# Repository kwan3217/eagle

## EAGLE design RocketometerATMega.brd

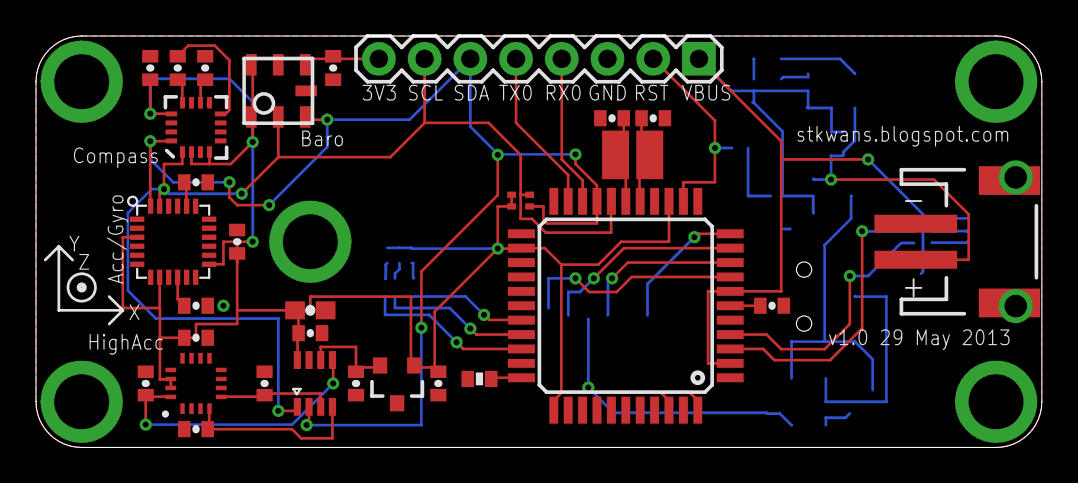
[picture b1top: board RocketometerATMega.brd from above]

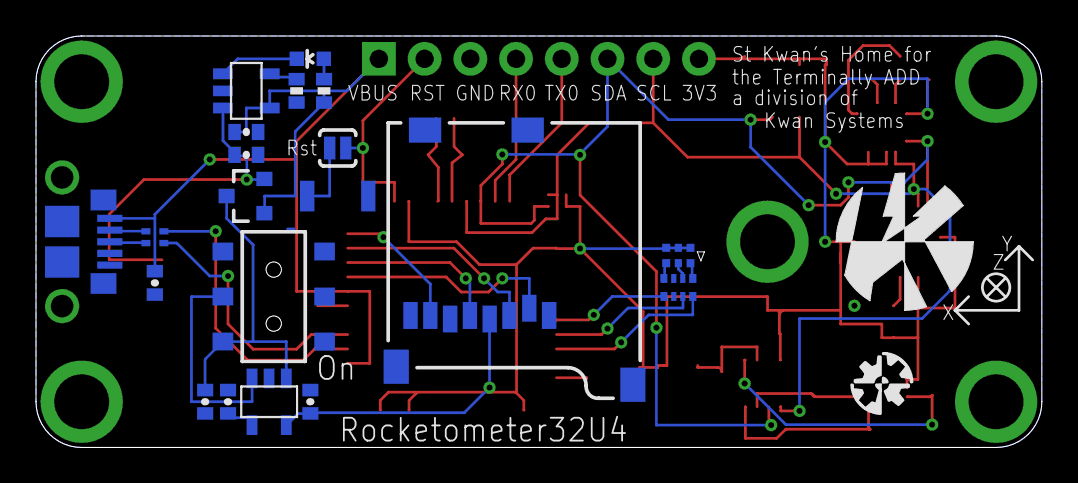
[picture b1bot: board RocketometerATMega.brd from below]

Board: 2 copper layers, 55.9 x 22.9 mm, 58 parts (22 on the bottom side), 43 nets.

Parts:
C101, C214, C610, C613, C802, C904, C905, C916, C917, C921: 100nF; 0402-CAP
C204, C406: 1uF; 0402-CAP
C215, C301, C302, C450, C810, C914, C922: 4.7uF; 0402-CAP
C416, C417: 22pF; 0402-CAP
C620: 2.2nF; 0402-CAP
C808: 220nF; 0402-CAP
C918: 10uF; 0603-CAP
D301: YELLOW; LED-0603
D302: DCC; SOT-23-3
D402: RGB; SMLP36
J301: JST 2mm; JST-2-SMD
J400: USB_MICROB_JSTGCT; USB_MICROB_3075
J401: M07; 1X08
J701: MICROSD-SOCKET; MICROSD-SOCKET-PP
JP1, JP2, JP3, JP4, JP5: STANDOFF
R301, R433: 10k; 0402-RES
R302: 1.5k; 0402-RES
R401: 10k; CRA02
R402: 1.5k; CRA04
R420: 22; CRA02
S201: AYZ0202
S457: B3U-1000P
S457A: SJ_2S-NO
U101: BMP180
U201: 3.3V; SOT-23-5
U301: MCP73831; SOT-23-5
U401: ATMEGA32U4TQFP; SPARKFUN-DIGITALIC_TQFP44
U601: MPU6050; MPU60X0
U801: HMC5883L; 16LPCC
U900: ADXL377
U910: AD7991; SOT-23-8
U920: MCP1525; SOT-23-3
U$4: AXES
U$5: KWAN_ACC
U$6: OSHW_ACC
Y401: 8MHz; CRYSTAL_SMD_3_2MM_2_5MM

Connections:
CS0: J701.2, U401.8
D+: J400.3, R420.2
D-: J400.2, R420.1
GND: C101.2, C204.2, C214.2, C215.2, C301.2, C302.2, C406.2, C416.1, C417.1, C450.2, C610.2, C613.1, C620.1, C802.2, C810.2, C904.2, C905.2, C914.2, C916.2, C917.2, C918.2, C921.2, C922.2, J301.1, J400.5, J400.P$1, J400.P$2, J400.P$3, J400.P$4, J400.P$8, J400.P$10, J401.3, J701.6, J701.CD2, J701.GND1, J701.GND3, JP1.P$1, JP2.P$1, JP3.P$1, JP4.P$1, JP5.P$1, R301.1, R433.1, S201.3, S457.P$2, U101.7, U201.2, U301.2, U401.5, U401.15, U401.23, U401.35, U401.43, U601.1, U601.9, U601.11, U601.18, U801.9, U801.11, U900.2, U900.6, U900.7, U910.7, U920.3
HWB: R433.2, U401.33
MISO0: J701.7, U401.11
MOSI0: J701.3, U401.10
unnamed: C620.2, U601.20
unnamed: R301.2, U301.5
unnamed: S457.P$1, S457A.1
unnamed: D301.C, U301.1
unnamed: D301.A, R302.1
unnamed: C922.1, U910.6, U920.2
unnamed: C610.1, U601.10
unnamed: C808.1, U801.8
unnamed: C808.2, U801.12
unnamed: C810.1, U801.10
unnamed: C214.1, U201.4
PWMB: R402.8, U401.31
PWMG: R402.7, U401.30
PWMR: R402.5, U401.29
PWR_EN: S201.2, U201.3
QWMB: D402.1, R402.1
QWMG: D402.3, R402.2
QWMR: D402.5, R402.4
RD+: R420.3, U401.4
RD-: R420.4, U401.3
RESET: J401.2, S457A.2, U401.13
RX0: J401.4, U401.20
SCK0: J701.5, U401.9
SCL0: J401.7, R401.2, U101.5, U401.18, U601.23, U801.1, U910.1
SDA0: J401.6, R401.1, U101.6, U401.19, U601.24, U801.16, U910.2
TX0: J401.5, U401.21
UCAP: C406.1, U401.6
VBUS: C302.1, C450.1, D302.1, J400.1, J401.1, R302.2, U301.4, U401.2, U401.7
VCC: C101.1, C215.1, C613.2, C802.1, C914.1, C917.1, C918.1, C921.1, D402.2, D402.4, D402.6, J401.8, J701.4, R401.3, R401.4, U101.2, U101.3, U201.5, U401.14, U401.24, U401.34, U401.42, U401.44, U601.3, U601.8, U601.13, U801.2, U801.4, U801.13, U900.14, U900.15, U910.8, U920.1
VIN: C204.1, D302.3, S201.1, U201.1
VLIPO: C301.1, D302.2, J301.2, U301.3
XACC: C905.1, U900.5, U910.3
XTAL1: C417.2, U401.17, Y401.2
XTAL2: C416.2, U401.16, Y401.1
YACC: C904.1, U900.4, U910.4
ZACC: C916.1, U900.16, U910.5

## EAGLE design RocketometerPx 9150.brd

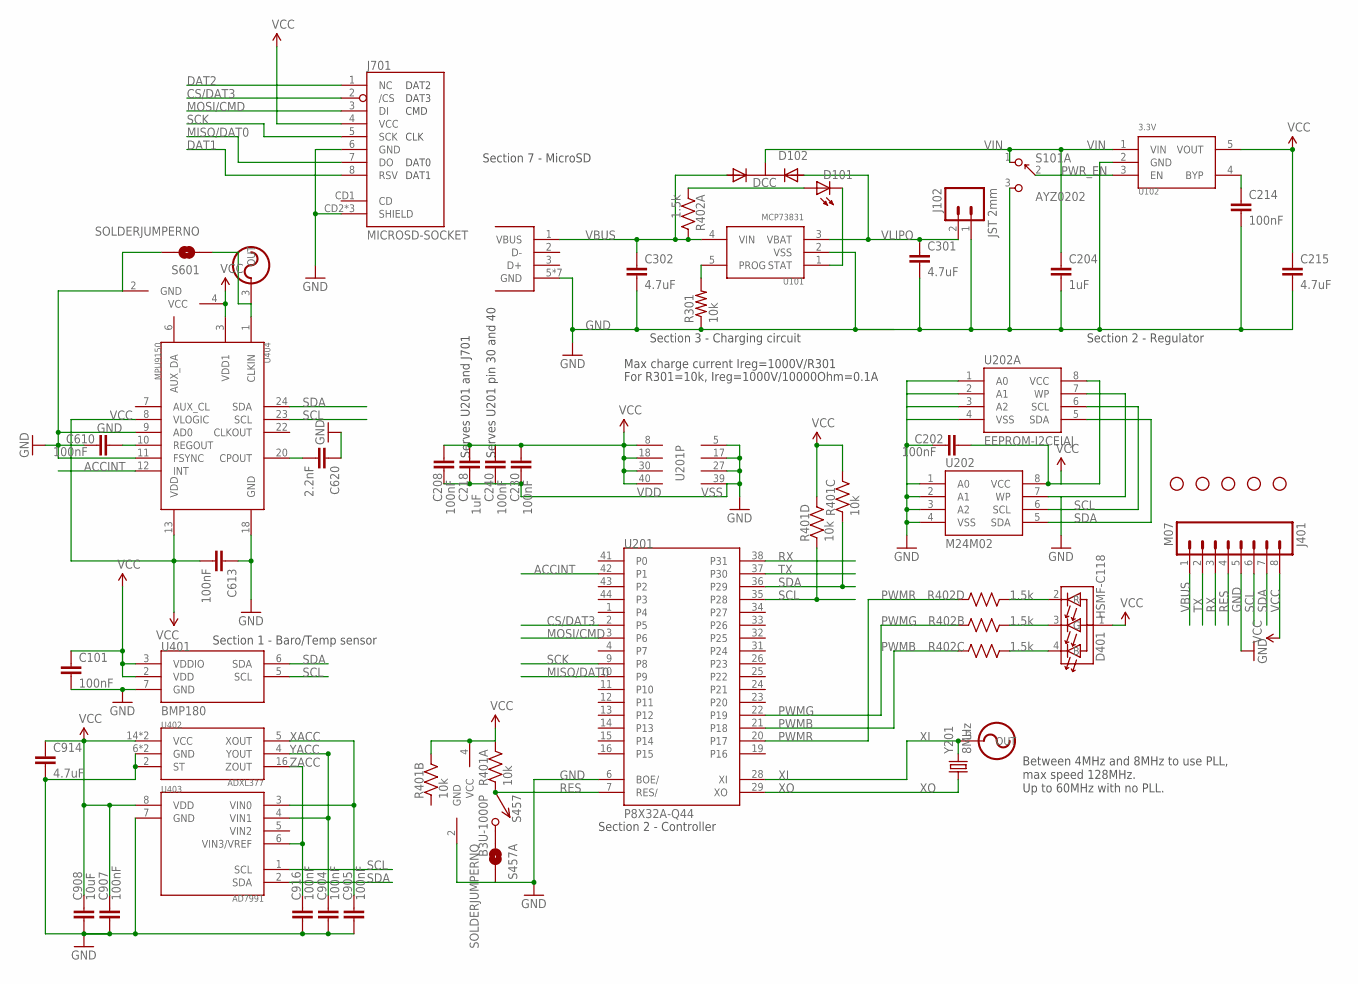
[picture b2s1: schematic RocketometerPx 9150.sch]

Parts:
C101, C202, C208, C214, C230, C240, C610, C613, C904, C905, C907, C916: 100nF; 0402-CAP; DIGIKEY 445-1265-1-ND
C204, C218: 1uF; 0402-CAP; DIGIKEY 445-4114-1-ND
C215, C301, C302, C914: 4.7uF; 0402-CAP; DIGIKEY 445-7395-1-ND
C620: 2.2nF; 0402-CAP; DIGIKEY 445-1257-1-ND
C908: 10uF; 0603-CAP; DIGIKEY 445-7486-1-ND
D101: YELLOW; LED-0603; DIGIKEY 350-2032-1-ND
D102: DCC; SOT-23-3; DIGIKEY 568-6500-1-ND
D401: HSMF-C118; DIGIKEY 516-1778-1-ND
J101: USB_MICROB_JSTGCT; USB_MICROB_3075; DIGIKEY 455-2562-1-ND
J102: JST 2mm; JST-2-SMD; DIGIKEY 455-1749-1-ND
J401: M07; 1X08; DIGIKEY $NOPART
J701: MICROSD-SOCKET; MICROSD-SOCKET-PP; DIGIKEY 101-00581-59-1-ND
JP1, JP2, JP3, JP4, JP5: STAND-OFFTIGHT; STAND-OFF-TIGHT; DIGIKEY $NOPART
R301: 10k; 0402-RES; DIGIKEY P10.0KLCT-ND
R401: 10k; CRA04; DIGIKEY CRA4S810KCT-ND
R402: 1.5k; CRA04; DIGIKEY CRA4S81.5KCT-ND
S101: AYZ0202; DIGIKEY 401-2013-1-ND
S457: B3U-1000P; DIGIKEY SW1020CT-ND
S457A, S601: SOLDERJUMPERNO; SJ_2S-NO; DIGIKEY $NOPART
U101: MCP73831; SOT-23-5; DIGIKEY 576-1910-1-ND
U102: 3.3V; SOT-23-5; DIGIKEY 576-1910-1-ND
U201: P8X32A-Q44; DIGIKEY P8X32A-Q44-ND
U202: M24M02; SO8N; DIGIKEY 497-11600-1-ND
U202A: EEPROM-I2CEIAJ; SO08-EIAJ; DIGIKEY $NOPART
U401: BMP180; DIGIKEY 828-1027-1-ND
U402: ADXL377; DIGIKEY ADXL377BCPZ-RL7CT-ND
U403: AD7991; SOT-23-8; DIGIKEY AD7991YRJZ-0500RL7CT-ND
U404: MPU9150; MPU60X0; DIGIKEY $NOPART
Y201: 8MHz; CRYSTAL_SMD_3_2MM_2_5MM; DIGIKEY 644-1178-1-ND
Y202: 8MHz; CRYSTAL_SMD_5MM_3_2MM
Y401: 19.2MHz; CRYSTAL_SMD_5MM_3_2MM

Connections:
ACCINT: U201.42 (P1), U404.12 (INT)
CS/DAT3: J701.2 (/CS), U201.2 (P5)
DAT1: J701.8 (RSV)
DAT2: J701.1 (NC)
GND: C101.2, C202.2, C204.2, C208.2, C214.2, C215.2, C218.2, C230.2, C240.2, C301.2, C302.2, C610.2, C613.1, C620.1, C904.2, C905.2, C907.2, C908.2, C914.2, C916.2, J101.5 (GND), J101.P$1 (GND), J101.P$2 (GND), J101.P$3 (GND), J101.P$4 (GND), J101.P$8 (GND), J101.P$10 (GND), J102.1, J401.5, J701.6 (GND), J701.CD2 (SHIELD), J701.GND1 (SHIELD), J701.GND3 (SHIELD), R301.1, S101.3, S457A.2, S601.2, U101.2 (VSS), U102.2 (GND), U201.5 (VSS), U201.6 (BOE/), U201.17 (VSS), U201.27 (VSS), U201.39 (VSS), U202.1 (A0), U202.2 (A1), U202.3 (A2), U202.4 (VSS), U202.7 (WP), U202A.1 (A0), U202A.2 (A1), U202A.3 (A2), U202A.4 (VSS), U202A.7 (WP), U401.7 (GND), U402.2 (ST), U402.6 (GND), U402.7 (GND), U403.7 (GND), U404.9 (AD0), U404.11 (FSYNC), U404.18 (GND), Y202.2 (GND), Y401.2 (GND)
MISO/DAT0: J701.7 (DO), U201.10 (P9)
MOSI/CMD: J701.3 (DI), U201.3 (P6)
unnamed: C620.2, U404.20 (CPOUT)
unnamed: R301.2, U101.5 (PROG)
unnamed: S601.1, U404.1 (CLKIN), Y401.3 (OUT)
unnamed: D101.C, U101.1 (STAT)
unnamed: D101.A, R402.1
unnamed: S457.P$2 (2), S457A.1
unnamed: C610.1, U404.10 (REGOUT)
unnamed: C214.1, U102.4 (BYP)
PWMB: R402.6 (2), U201.21 (P18)
PWMG: R402.7 (2), U201.22 (P19)
PWMR: R402.5 (2), U201.20 (P17)
PWR_EN: S101.2, U102.3 (EN)
QWMB: D401.4 (B), R402.3 (1)
QWMG: D401.3 (G), R402.2 (1)
QWMR: D401.2 (R), R402.4 (1)
RES: J401.4, R401.1, S457.P$1 (1), U201.7 (RES/)
RX: J401.3, U201.38 (P31)
SCK: J701.5 (SCK), U201.9 (P8)
SCL: J401.6, R401.4 (1), U201.35 (P28), U202.6 (SCL), U202A.6 (SCL), U401.5 (SCL), U403.1 (SCL), U404.23 (SCL)
SDA: J401.7, R401.3 (1), U201.36 (P29), U202.5 (SDA), U202A.5 (SDA), U401.6 (SDA), U403.2 (SDA), U404.24 (SDA)
TX: J401.2, U201.37 (P30)
VBUS: C302.1, D102.1 (A1), J101.1 (VBUS), J401.1, R402.8 (2), U101.4 (VIN)
VCC: C101.1, C202.1, C208.1, C215.1, C218.1, C230.1, C240.1, C613.2, C907.1, C908.1, C914.1, D401.1 (A), J401.8, J701.4 (VCC), R401.5 (2), R401.6 (2), R401.7 (2), R401.8 (2), U102.5 (VOUT), U201.8 (VDD), U201.18 (VDD), U201.30 (VDD), U201.40 (VDD), U202.8 (VCC), U202A.8 (VCC), U401.2 (VDD), U401.3 (VDDIO), U402.14 (VCC), U402.15 (VCC), U403.8 (VDD), U404.3 (VDD1), U404.8 (VLOGIC), U404.13 (VDD), Y202.4 (VCC), Y401.4 (VCC)
VIN: C204.1, D102.3 (K), S101.1, U102.1 (VIN)
VLIPO: C301.1, D102.2 (A2), J102.2, U101.3 (VBAT)
XACC: C905.1, U402.5 (XOUT), U403.3 (VIN0)
XI: U201.28 (XI), Y201.2, Y202.3 (OUT)
XO: U201.29 (XO), Y201.1
YACC: C904.1, U402.4 (YOUT), U403.4 (VIN1)
ZACC: C916.1, U402.16 (ZOUT), U403.6 (VIN3/VREF)

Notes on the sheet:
Section 2 - Regulator
Section 3 - Charging circuit
Section 7 - MicroSD
Section 1 - Baro/Temp sensor
Max charge current Ireg=1000V/R301
For R301=10k, Ireg=1000V/10000Ohm=0.1A
Section 2 - Controller
Serves U201 and J701
Serves U201 pin 30 and 40
Between 4MHz and 8MHz to use PLL, max speed 128MHz. Up to 60MHz with no PLL.

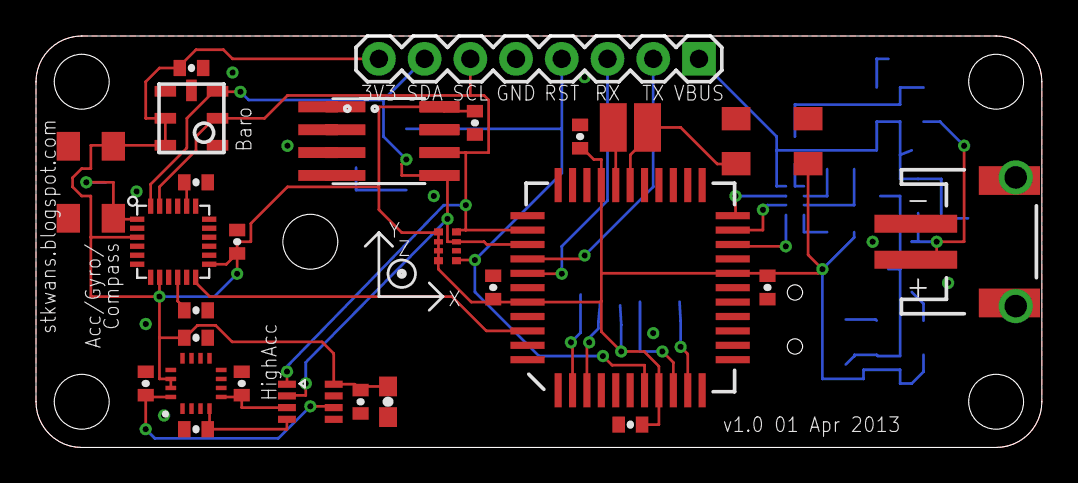
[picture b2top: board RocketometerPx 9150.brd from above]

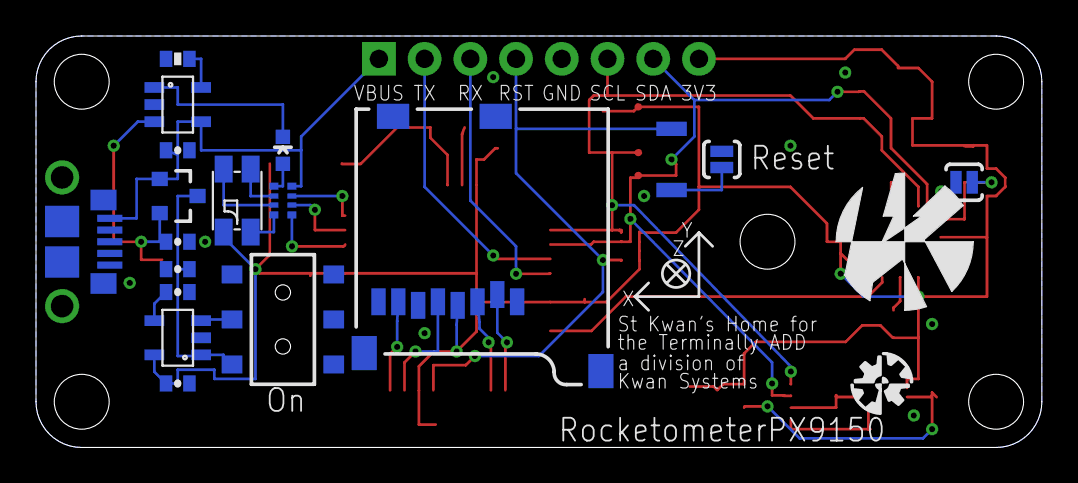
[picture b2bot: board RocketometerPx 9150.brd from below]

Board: 2 copper layers, 55.9 x 22.9 mm, 54 parts (20 on the bottom side), 35 nets.

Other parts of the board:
U$4: AXES
U$5: KWAN_ACC
U$6: OSHW_ACC

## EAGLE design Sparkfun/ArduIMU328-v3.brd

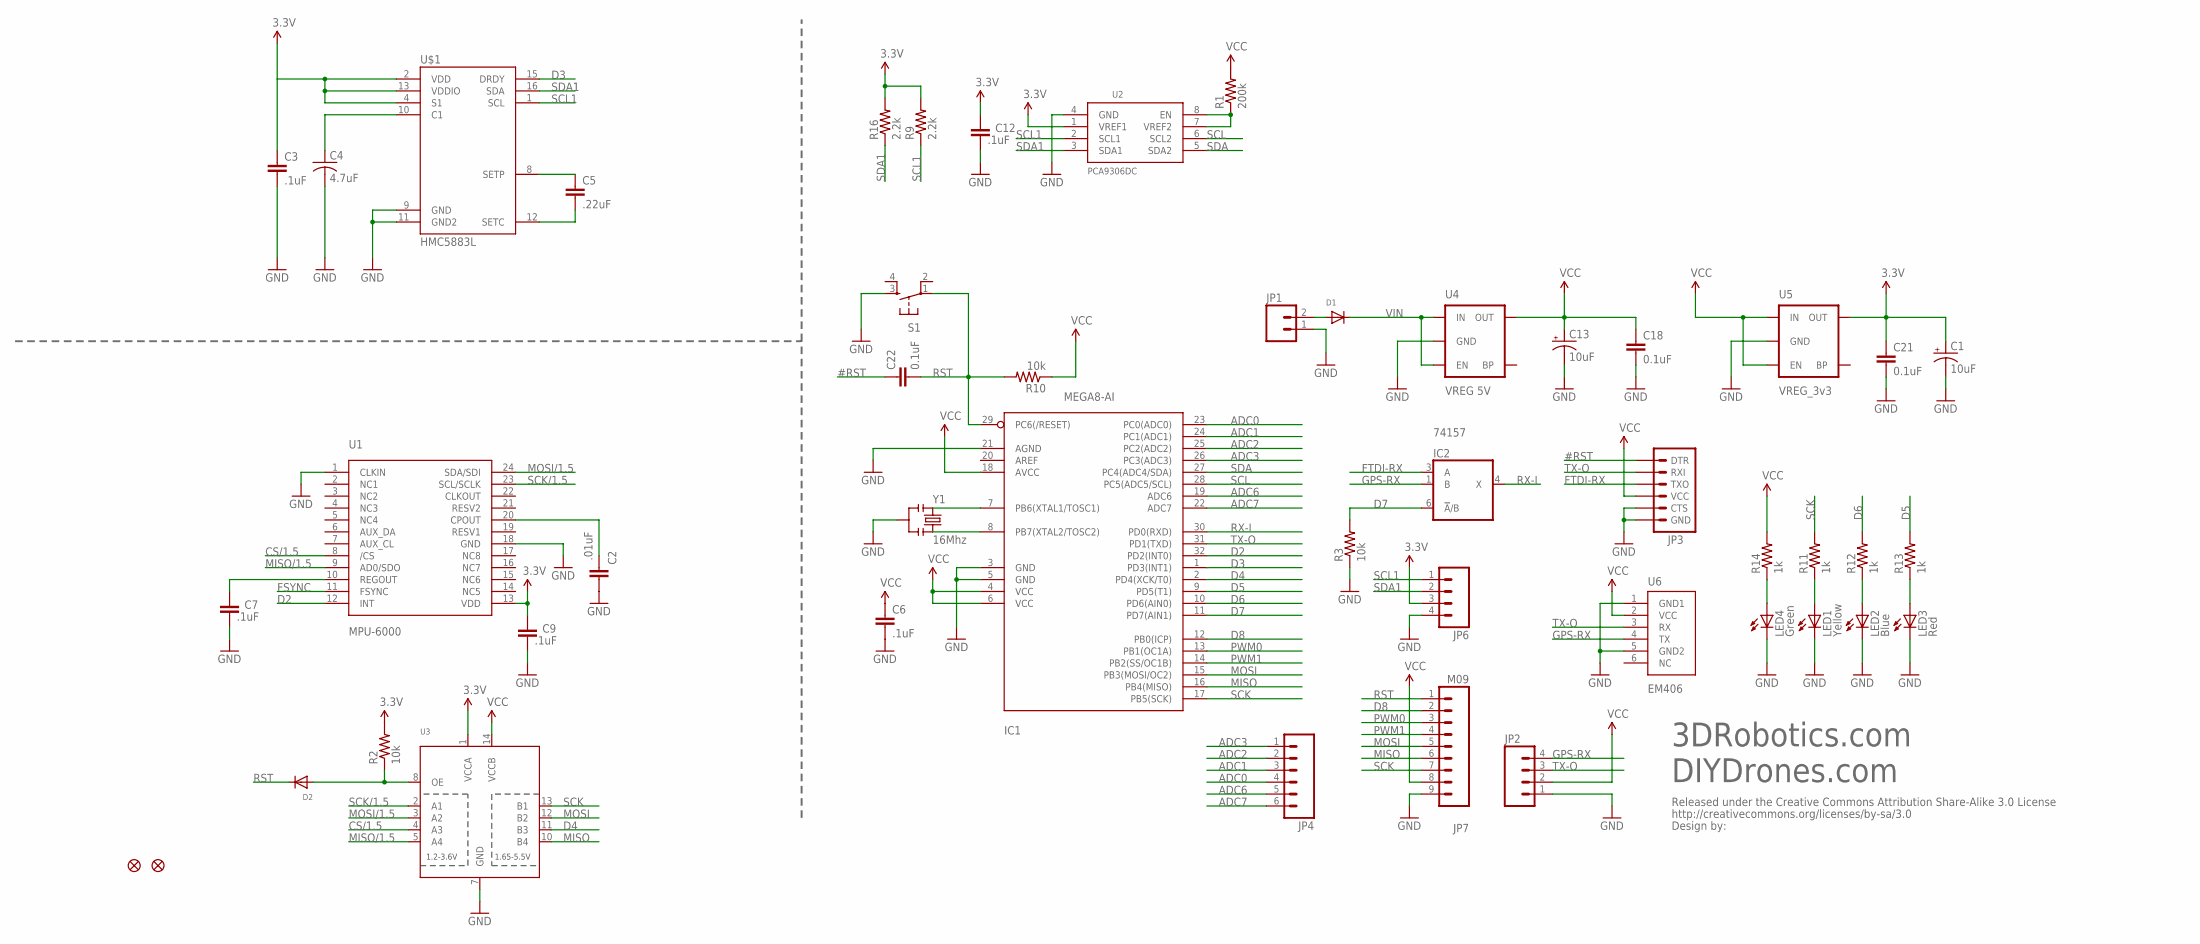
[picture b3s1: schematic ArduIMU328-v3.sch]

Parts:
C1, C13: 10uF; EIA3216
C2: .01uF; C0402
C3, C6: .1uF; 0402-CAP
C4: 4.7uF; C1206
C5: .22uF; 0402-CAP
C7, C9, C12: .1uF; C0402
C18, C21, C22: 0.1uF; 0402-CAP
D1, D2: DIODESOD-123; SOD-123
IC1: MEGA8-AI; TQFP32-08
IC2: 74157; DBV_R-PDSO-G6
JP1: M02PTH; 1X02
JP2, JP6: M04PTH; 1X04
JP3: ARDUINO_SERIAL_PROGRAMPTH; 1X06
JP4: M06SIP; 1X06
JP5, JP8: FIDUCIAL1X2; FIDUCIAL-1X2
JP7: M09; 1X09
LED1: Yellow; LED-0603
LED2: Blue; LED-0603
LED3: Red; LED-0603
LED4: Green; LED-0603
R1: 200k; C0402
R2, R3, R10: 10k; 0402-RES
R9, R16: 2.2k; C0402
R11, R12, R13, R14: 1k; 0402-RES
S1: TAC_SWITCHSMD; TACTILE_SWITCH_SMD
U1: MPU-6000; QFN-24
U2: PCA9306DC; VSSOP8
U3: TXB0104PWR; TSSOP14
U4: VREG 5V; SOT23-5
U5: VREG_3v3; SOT23-5
U6: EM406
U$1: HMC5883L; LPCC16
U$2: CREATIVE_COMMONS
Y1: 16Mhz; RESONATOR-SMD

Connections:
3.3V: C1.A (+), C3.1, C9.2, C12.2, C21.1, JP6.3, R2.2, R9.2, R16.2, U1.13 (VDD), U2.1 (VREF1), U3.1 (VCCA), U5.5 (OUT), U$1.2 (VDD), U$1.4 (S1), U$1.13 (VDDIO)
#RST: C22.1, JP3.1 (DTR)
ADC0: IC1.23 (PC0(ADC0)), JP4.4
ADC1: IC1.24 (PC1(ADC1)), JP4.3
ADC2: IC1.25 (PC2(ADC2)), JP4.2
ADC3: IC1.26 (PC3(ADC3)), JP4.1
ADC6: IC1.19 (ADC6), JP4.5
ADC7: IC1.22 (ADC7), JP4.6
CS/1.5: U1.8 (/CS), U3.4 (A3)
D2: IC1.32 (PD2(INT0)), U1.12 (INT)
D3: IC1.1 (PD3(INT1)), U$1.15 (DRDY)
D4: IC1.2 (PD4(XCK/T0)), U3.11 (B3)
D5: IC1.9 (PD5(T1)), R13.2
D6: IC1.10 (PD6(AIN0)), R12.2
D7: IC1.11 (PD7(AIN1)), IC2.6 (!A!/B), R3.2
D8: IC1.12 (PB0(ICP)), JP7.2
FSYNC: U1.11 (FSYNC)
FTDI-RX: IC2.3 (A), JP3.3 (TXO)
GND: C1.C (-), C2.1, C3.2, C4.2, C6.2, C7.1, C9.1, C12.1, C13.C (-), C18.2, C21.2, IC1.3 (GND), IC1.5 (GND), IC1.21 (AGND), IC2.2 (GND), JP1.1, JP2.1, JP3.5 (CTS), JP3.6 (GND), JP6.4, JP7.9, LED1.C, LED2.C, LED3.C, LED4.C, R3.1, S1.3, U1.1 (CLKIN), U1.18 (GND), U2.4 (GND), U3.7 (GND), U4.2 (GND), U5.2 (GND), U6.1 (GND1), U6.5 (GND2), U$1.9 (GND), U$1.11 (GND2), Y1.2
GPS-RX: IC2.1 (B), JP2.4, U6.4 (TX)
MISO: IC1.16 (PB4(MISO)), JP7.6, U3.10 (B4)
MISO/1.5: U1.9 (AD0/SDO), U3.5 (A4)
MOSI: IC1.15 (PB3(MOSI/OC2)), JP7.5, U3.12 (B2)
MOSI/1.5: U1.24 (SDA/SDI), U3.3 (A2)
unnamed: R1.1, U2.7 (VREF2), U2.8 (EN)
unnamed: C2.2, U1.20 (CPOUT)
unnamed: C7.2, U1.10 (REGOUT)
unnamed: C4.1, U$1.10 (C1)
unnamed: IC1.7 (PB6(XTAL1/TOSC1)), Y1.1
unnamed: C5.1, U$1.8 (SETP)
unnamed: IC1.8 (PB7(XTAL2/TOSC2)), Y1.3
unnamed: C5.2, U$1.12 (SETC)
unnamed: D2.A, R2.1, U3.8 (OE)
unnamed: LED1.A, R11.1
unnamed: LED2.A, R12.1
unnamed: LED3.A, R13.1
unnamed: D1.A, JP1.2
unnamed: LED4.A, R14.1
PWM0: IC1.13 (PB1(OC1A)), JP7.3
PWM1: IC1.14 (PB2(SS/OC1B)), JP7.4
RST: C22.2, D2.C, IC1.29 (PC6(/RESET)), JP7.1, R10.2, S1.1
RX-I: IC1.30 (PD0(RXD)), IC2.4 (X)
SCK: IC1.17 (PB5(SCK)), JP7.7, R11.2, U3.13 (B1)
SCK/1.5: U1.23 (SCL/SCLK), U3.2 (A1)
SCL: IC1.28 (PC5(ADC5/SCL)), U2.6 (SCL2)
SCL1: JP6.1, R9.1, U2.2 (SCL1), U$1.1 (SCL)
SDA: IC1.27 (PC4(ADC4/SDA)), U2.5 (SDA2)
SDA1: JP6.2, R16.1, U2.3 (SDA1), U$1.16 (SDA)
TX-O: IC1.31 (PD1(TXD)), JP2.3, JP3.2 (RXI), U6.3 (RX)
VCC: C6.1, C13.A (+), C18.1, IC1.4 (VCC), IC1.6 (VCC), IC1.18 (AVCC), IC2.5 (VCC), JP2.2, JP3.4 (VCC), JP7.8, R1.2, R10.1, R14.2, U3.14 (VCCB), U4.5 (OUT), U5.1 (IN), U5.3 (EN), U6.2 (VCC)
VIN: D1.C, U4.1 (IN), U4.3 (EN)

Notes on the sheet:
DIYDrones.com
3DRobotics.com

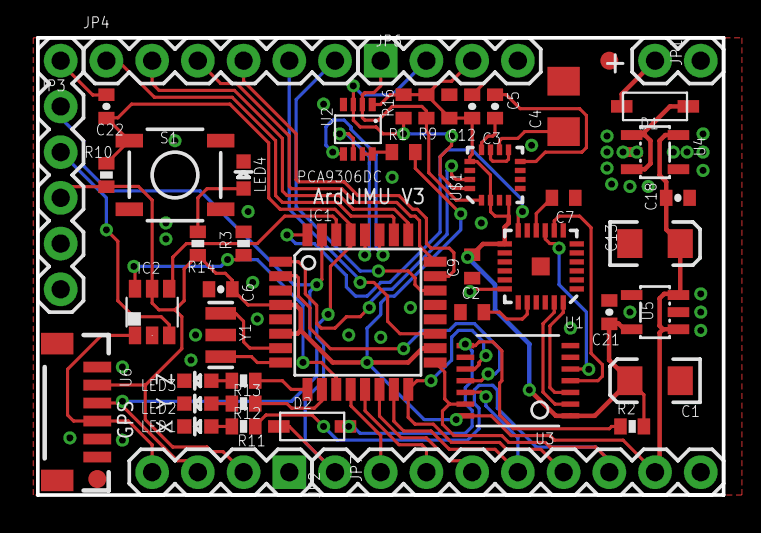
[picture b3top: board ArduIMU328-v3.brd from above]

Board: 4 copper layers, 38.1 x 25.4 mm, 49 parts (0 on the bottom side), 50 nets.

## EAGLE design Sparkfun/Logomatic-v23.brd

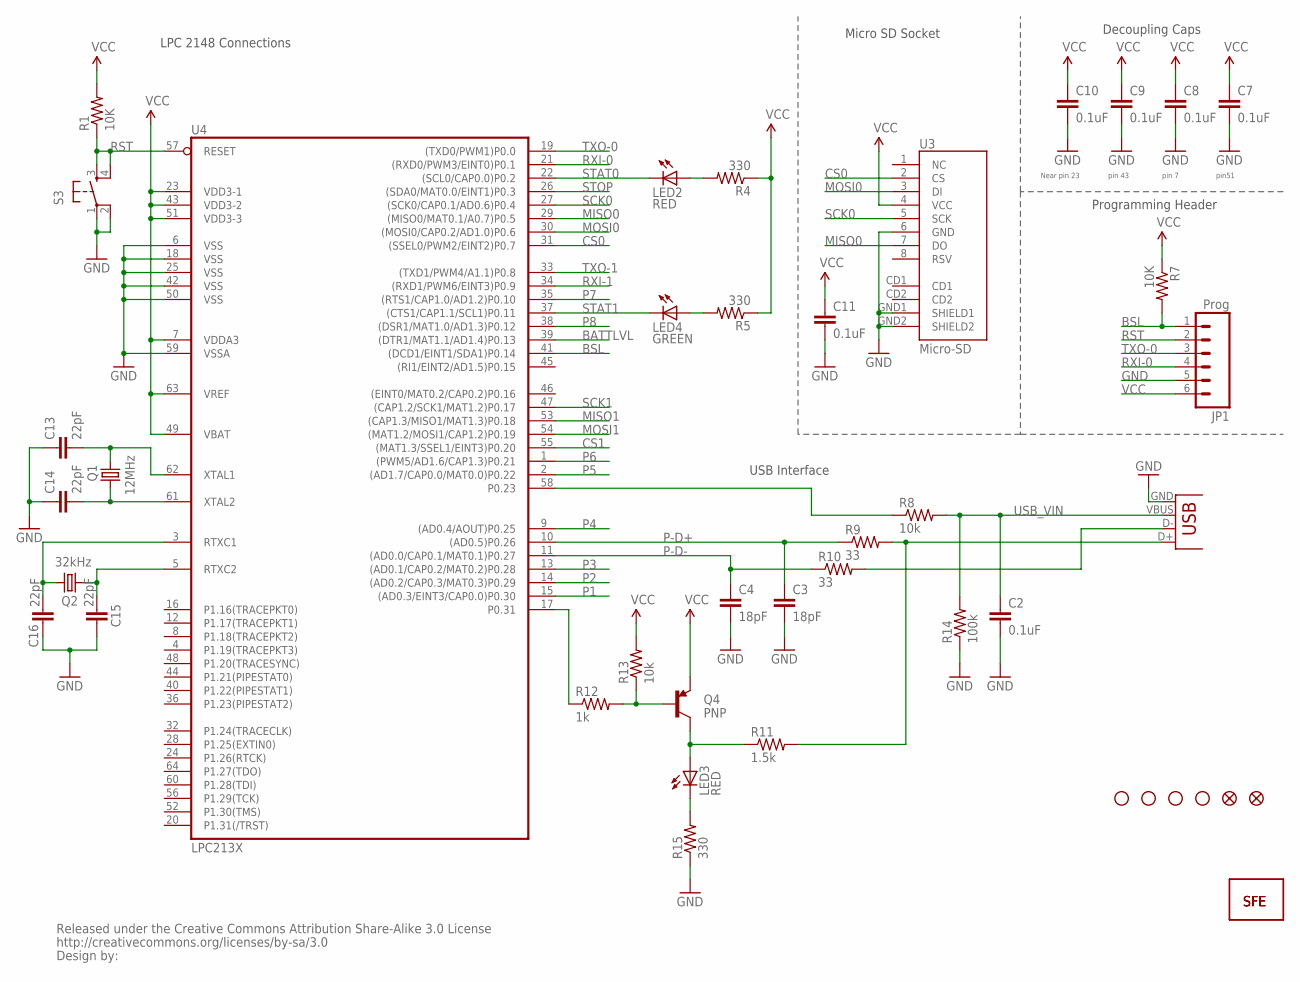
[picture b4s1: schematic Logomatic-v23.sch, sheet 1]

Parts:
C2, C7, C8, C9, C10, C11: 0.1uF; C0402
C3, C4: 18pF; C0402
C13, C14, C15, C16: 22pF; C0402
JP1: Prog; 1X06
LED2, LED3: RED; LED-0603
LED4: GREEN; LED-0603
Q1: 12MHz; CRYSTAL-SMD-5X3
Q2: 32kHz; CRYSTAL-32KHZ-SMD
Q4: PNP; SOT23-3
R1, R7: 10K; C0402
R4, R5, R15: 330; C0402
R8, R13: 10k; C0402
R9, R10: 33; C0402
R11: 1.5k; C0402
R12: 1k; C0402
R14: 100k; C0402
S3: Reset; TACTILE_SWITCH_SMD
U3: Micro-SD; USD-SOCKET-PP
U4: LPC213X; SQFP-S-10X10-64
U$1, U$2: FIDUCIAL1X2; FIDUCIAL-1X2
U$3, U$4, U$5, U$8: STAND-OFF
U$6: LOGO-SFENEW; SFE-NEW-WEBLOGO
U$7: LOGO-SFESK; SFE-LOGO-FLAME
U$9: CREATIVE_COMMONS
X1: USBSMD; USB-MINIB

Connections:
BATTLVL: U4.39 ((DTR1/MAT1.1/AD1.4)P0.13); also elsewhere on the board
BSL: JP1.1, R7.2, U4.41 ((DCD1/EINT1/SDA1)P0.14)
CS0: U3.2 (CS), U4.31 ((SSEL0/PWM2/EINT2)P0.7)
CS1: U4.55 ((MAT1.3/SSEL1/EINT3)P0.20); also elsewhere on the board
GND: C2.2, C3.2, C4.2, C7.2, C8.2, C9.2, C10.2, C11.2, C13.1, C14.1, C15.1, C16.1, JP1.5, R14.1, R15.1, S3.1, S3.2, U3.6 (GND), U3.GND1 (SHIELD1), U3.GND2 (SHIELD2), U4.6 (VSS), U4.18 (VSS), U4.25 (VSS), U4.42 (VSS), U4.50 (VSS), U4.59 (VSSA), X1.GND; also elsewhere on the board
MISO0: U3.7 (DO), U4.29 ((MISO0/MAT0.1/A0.7)P0.5)
MISO1: U4.53 ((CAP1.3/MISO1/MAT1.3)P0.18); also elsewhere on the board
MOSI0: U3.3 (DI), U4.30 ((MOSI0/CAP0.2/AD1.0)P0.6)
MOSI1: U4.54 ((MAT1.2/MOSI1/CAP1.2)P0.19); also elsewhere on the board
unnamed: C13.2, Q1.3 (2), U4.62 (XTAL1)
unnamed: C16.2, Q2.X2 (2), U4.3 (RTXC1)
unnamed: LED2.A, R4.2
unnamed: C15.2, Q2.X1 (1), U4.5 (RTXC2)
unnamed: R8.1, U4.58 (P0.23)
unnamed: Q4.1 (B), R12.2, R13.1
unnamed: LED4.A, R5.2
unnamed: C14.2, Q1.1, U4.61 (XTAL2)
unnamed: R12.1, U4.17 (P0.31)
unnamed: LED3.C, R15.2
P1: U4.15 ((AD0.3/EINT3/CAP0.0)P0.30); also elsewhere on the board
P2: U4.14 ((AD0.2/CAP0.3/MAT0.3)P0.29); also elsewhere on the board
P3: U4.13 ((AD0.1/CAP0.2/MAT0.2)P0.28); also elsewhere on the board
P4: U4.9 ((AD0.4/AOUT)P0.25); also elsewhere on the board
P5: U4.2 ((AD1.7/CAP0.0/MAT0.0)P0.22); also elsewhere on the board
P6: U4.1 ((PWM5/AD1.6/CAP1.3)P0.21); also elsewhere on the board
P7: U4.35 ((RTS1/CAP1.0/AD1.2)P0.10); also elsewhere on the board
P8: U4.38 ((DSR1/MAT1.0/AD1.3)P0.12); also elsewhere on the board
P-D+: C3.1, R9.1, U4.10 ((AD0.5)P0.26)
P-D-: C4.1, R10.1, U4.11 ((AD0.0/CAP0.1/MAT0.1)P0.27)
RST: JP1.2, R1.1, S3.3, S3.4, U4.57 (RESET)
RXI-0: JP1.4, U4.21 ((RXD0/PWM3/EINT0)P0.1)
RXI-1: U4.34 ((RXD1/PWM6/EINT3)P0.9); also elsewhere on the board
SCK0: U3.5 (SCK), U4.27 ((SCK0/CAP0.1/AD0.6)P0.4)
SCK1: U4.47 ((CAP1.2/SCK1/MAT1.2)P0.17); also elsewhere on the board
STAT: LED3.A, Q4.3 (C), R11.1
STAT0: LED2.C, U4.22 ((SCL0/CAP0.0)P0.2)
STAT1: LED4.C, U4.37 ((CTS1/CAP1.1/SCL1)P0.11)
STOP: U4.26 ((SDA0/MAT0.0/EINT1)P0.3); also elsewhere on the board
TXO-0: JP1.3, U4.19 ((TXD0/PWM1)P0.0)
TXO-1: U4.33 ((TXD1/PWM4/A1.1)P0.8); also elsewhere on the board
USB_D+: R9.2, R11.2, X1.D+
USB_D-: R10.2, X1.D-
USB_VIN: C2.1, R8.2, R14.2, X1.VBUS; also elsewhere on the board
VCC: C7.1, C8.1, C9.1, C10.1, C11.1, JP1.6, Q4.2 (E), R1.2, R4.1, R5.1, R7.1, R13.2, U3.4 (VCC), U4.7 (VDDA3), U4.23 (VDD3-1), U4.43 (VDD3-2), U4.49 (VBAT), U4.51 (VDD3-3), U4.63 (VREF); also elsewhere on the board

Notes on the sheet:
Near pin 23
pin 43
pin51
Decoupling Caps
Programming Header
USB Interface
Micro SD Socket
pin 7
LPC 2148 Connections

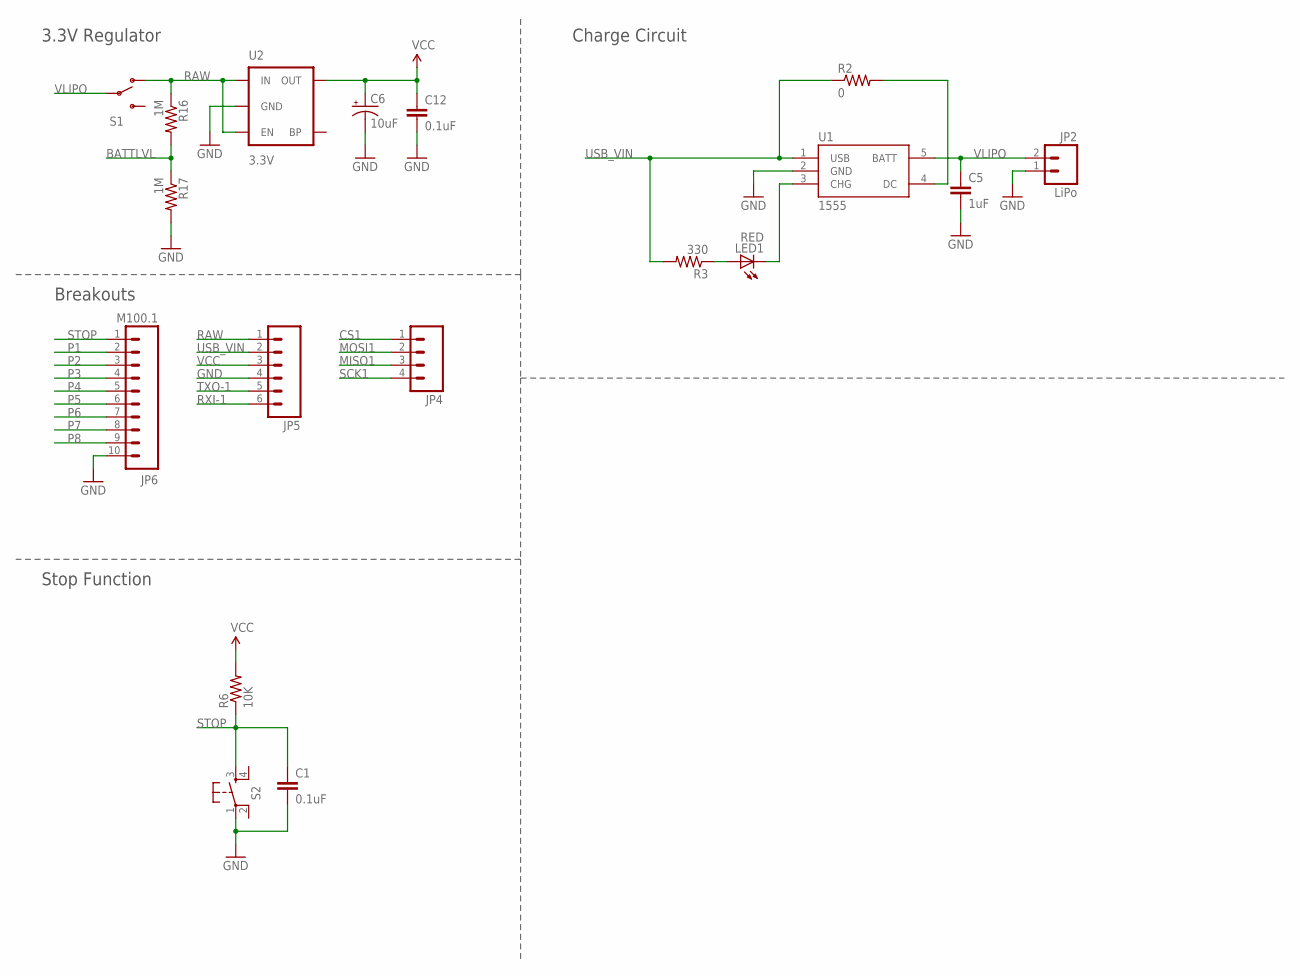
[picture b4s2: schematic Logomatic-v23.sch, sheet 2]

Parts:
C1, C12: 0.1uF; C0402
C5: 1uF; C0402
C6: 10uF; EIA3216
JP2: LiPo; S2B-PH
JP4: M04PTH; 1X04
JP5: M06SIP; 1X06
JP6: M100.1; 1X10
LED1: RED; LED-0603
R2: 0; C0402
R3: 330; C0402
R6: 10K; C0402
R16, R17: 1M; C0402
S1: SWITCH-SPSTSMD; AYZ0202
S2: Stop; TACTILE_SWITCH_SMD
U1: 1555; SOT23-5
U2: 3.3V; SOT23-5

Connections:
BATTLVL: R16.2, R17.1; also elsewhere on the board
CS1: JP4.1; also elsewhere on the board
GND: C1.2, C5.2, C6.C (-), C12.2, JP2.1, JP5.4, JP6.10, R17.2, S2.1, U1.2 (GND), U2.2 (GND); also elsewhere on the board
MISO1: JP4.3; also elsewhere on the board
MOSI1: JP4.2; also elsewhere on the board
unnamed: R2.2, U1.4 (DC)
unnamed: LED1.C, U1.3 (CHG)
unnamed: LED1.A, R3.1
P1: JP6.2; also elsewhere on the board
P2: JP6.3; also elsewhere on the board
P3: JP6.4; also elsewhere on the board
P4: JP6.5; also elsewhere on the board
P5: JP6.6; also elsewhere on the board
P6: JP6.7; also elsewhere on the board
P7: JP6.8; also elsewhere on the board
P8: JP6.9; also elsewhere on the board
RAW: JP5.1, R16.1, S1.1 (O), U2.1 (IN), U2.3 (EN)
RXI-1: JP5.6; also elsewhere on the board
SCK1: JP4.4; also elsewhere on the board
STOP: C1.1, JP6.1, R6.1, S2.3; also elsewhere on the board
TXO-1: JP5.5; also elsewhere on the board
USB_VIN: JP5.2, R2.1, R3.2, U1.1 (USB); also elsewhere on the board
VCC: C6.A (+), C12.1, JP5.3, R6.2, U2.5 (OUT); also elsewhere on the board
VLIPO: C5.1, JP2.2, S1.2, U1.5 (BATT)

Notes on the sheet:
3.3V Regulator
Charge Circuit
Breakouts
Stop Function

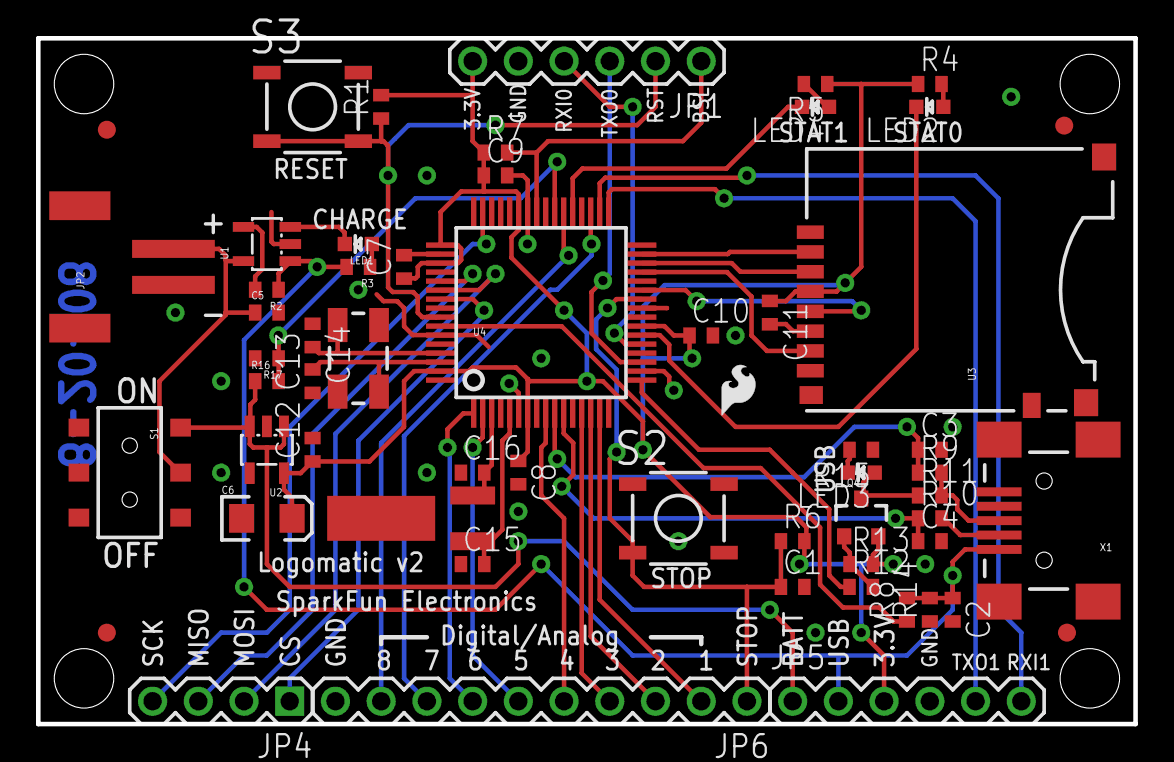
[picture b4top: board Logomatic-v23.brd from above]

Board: 2 copper layers, 61.0 x 38.1 mm, 64 parts (1 on the bottom side), 49 nets.

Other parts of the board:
E$1, E$2: FIDUCIAL-1X2

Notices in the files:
parts and their libraries:
SparkFun-Connectors: Licensing: CC v3.0 Share-Alike You are welcome to use this library for commercial purposes.
SparkFun: Released under the Creative Commons Attribution Share-Alike 3.0 License
SparkFun: http://creativecommons.org/licenses/by-sa/3.0
